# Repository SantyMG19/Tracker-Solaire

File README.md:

# Tracker-Solaire
Le Tracker Solaire est un système technologiques d'un panneau qui suit le mouvement du Soleil pour optimiser la capture d'énergie solaire.

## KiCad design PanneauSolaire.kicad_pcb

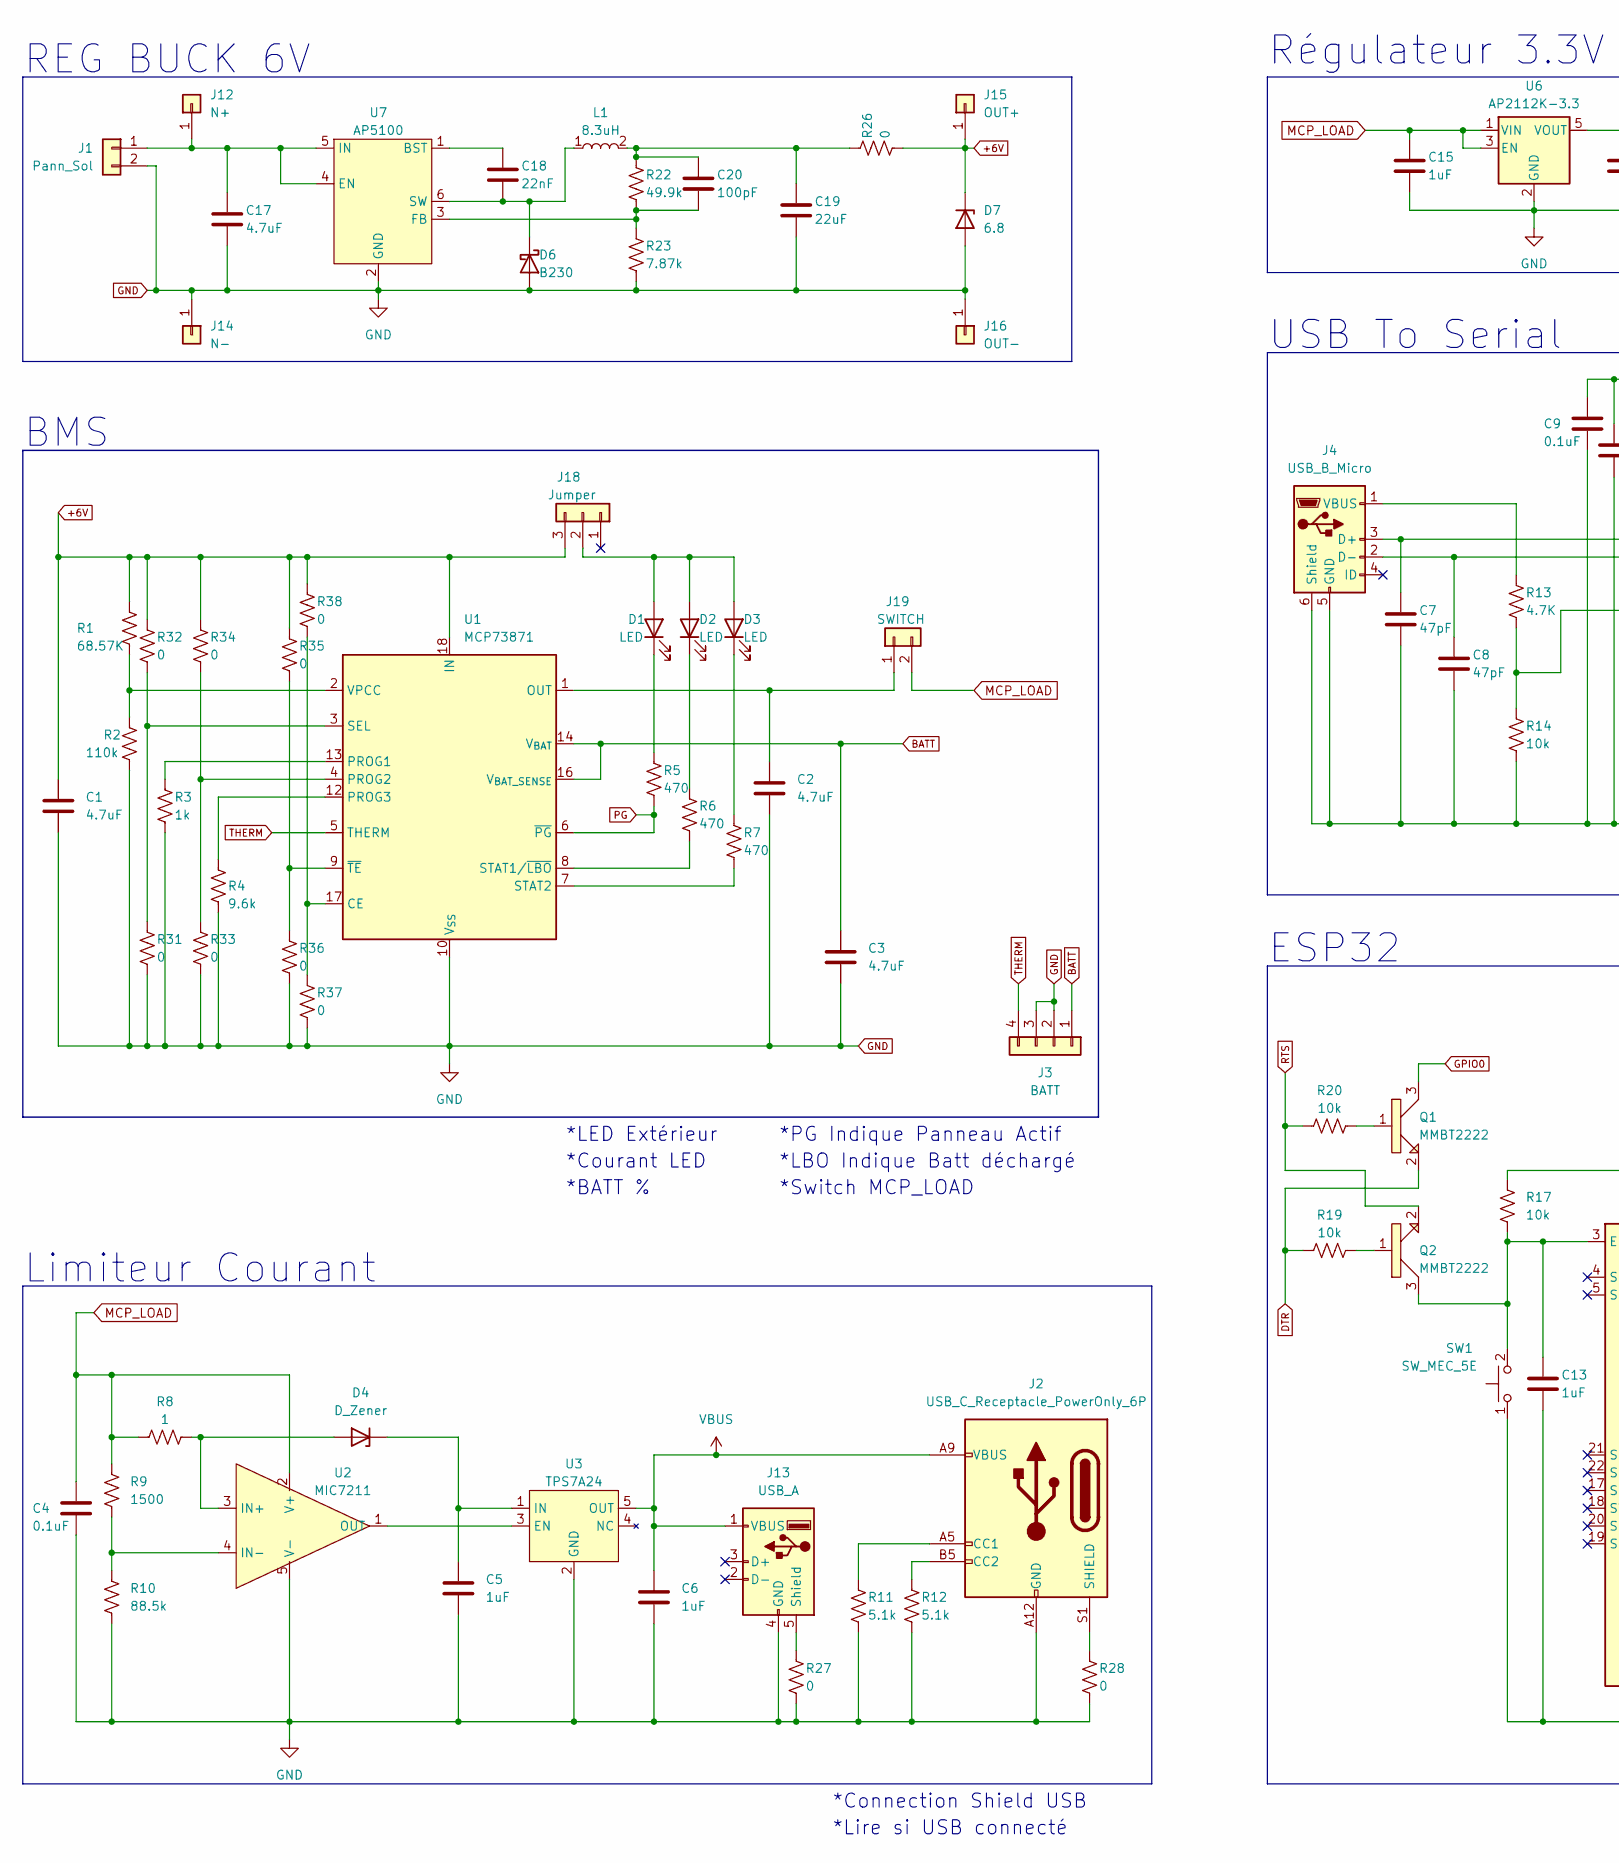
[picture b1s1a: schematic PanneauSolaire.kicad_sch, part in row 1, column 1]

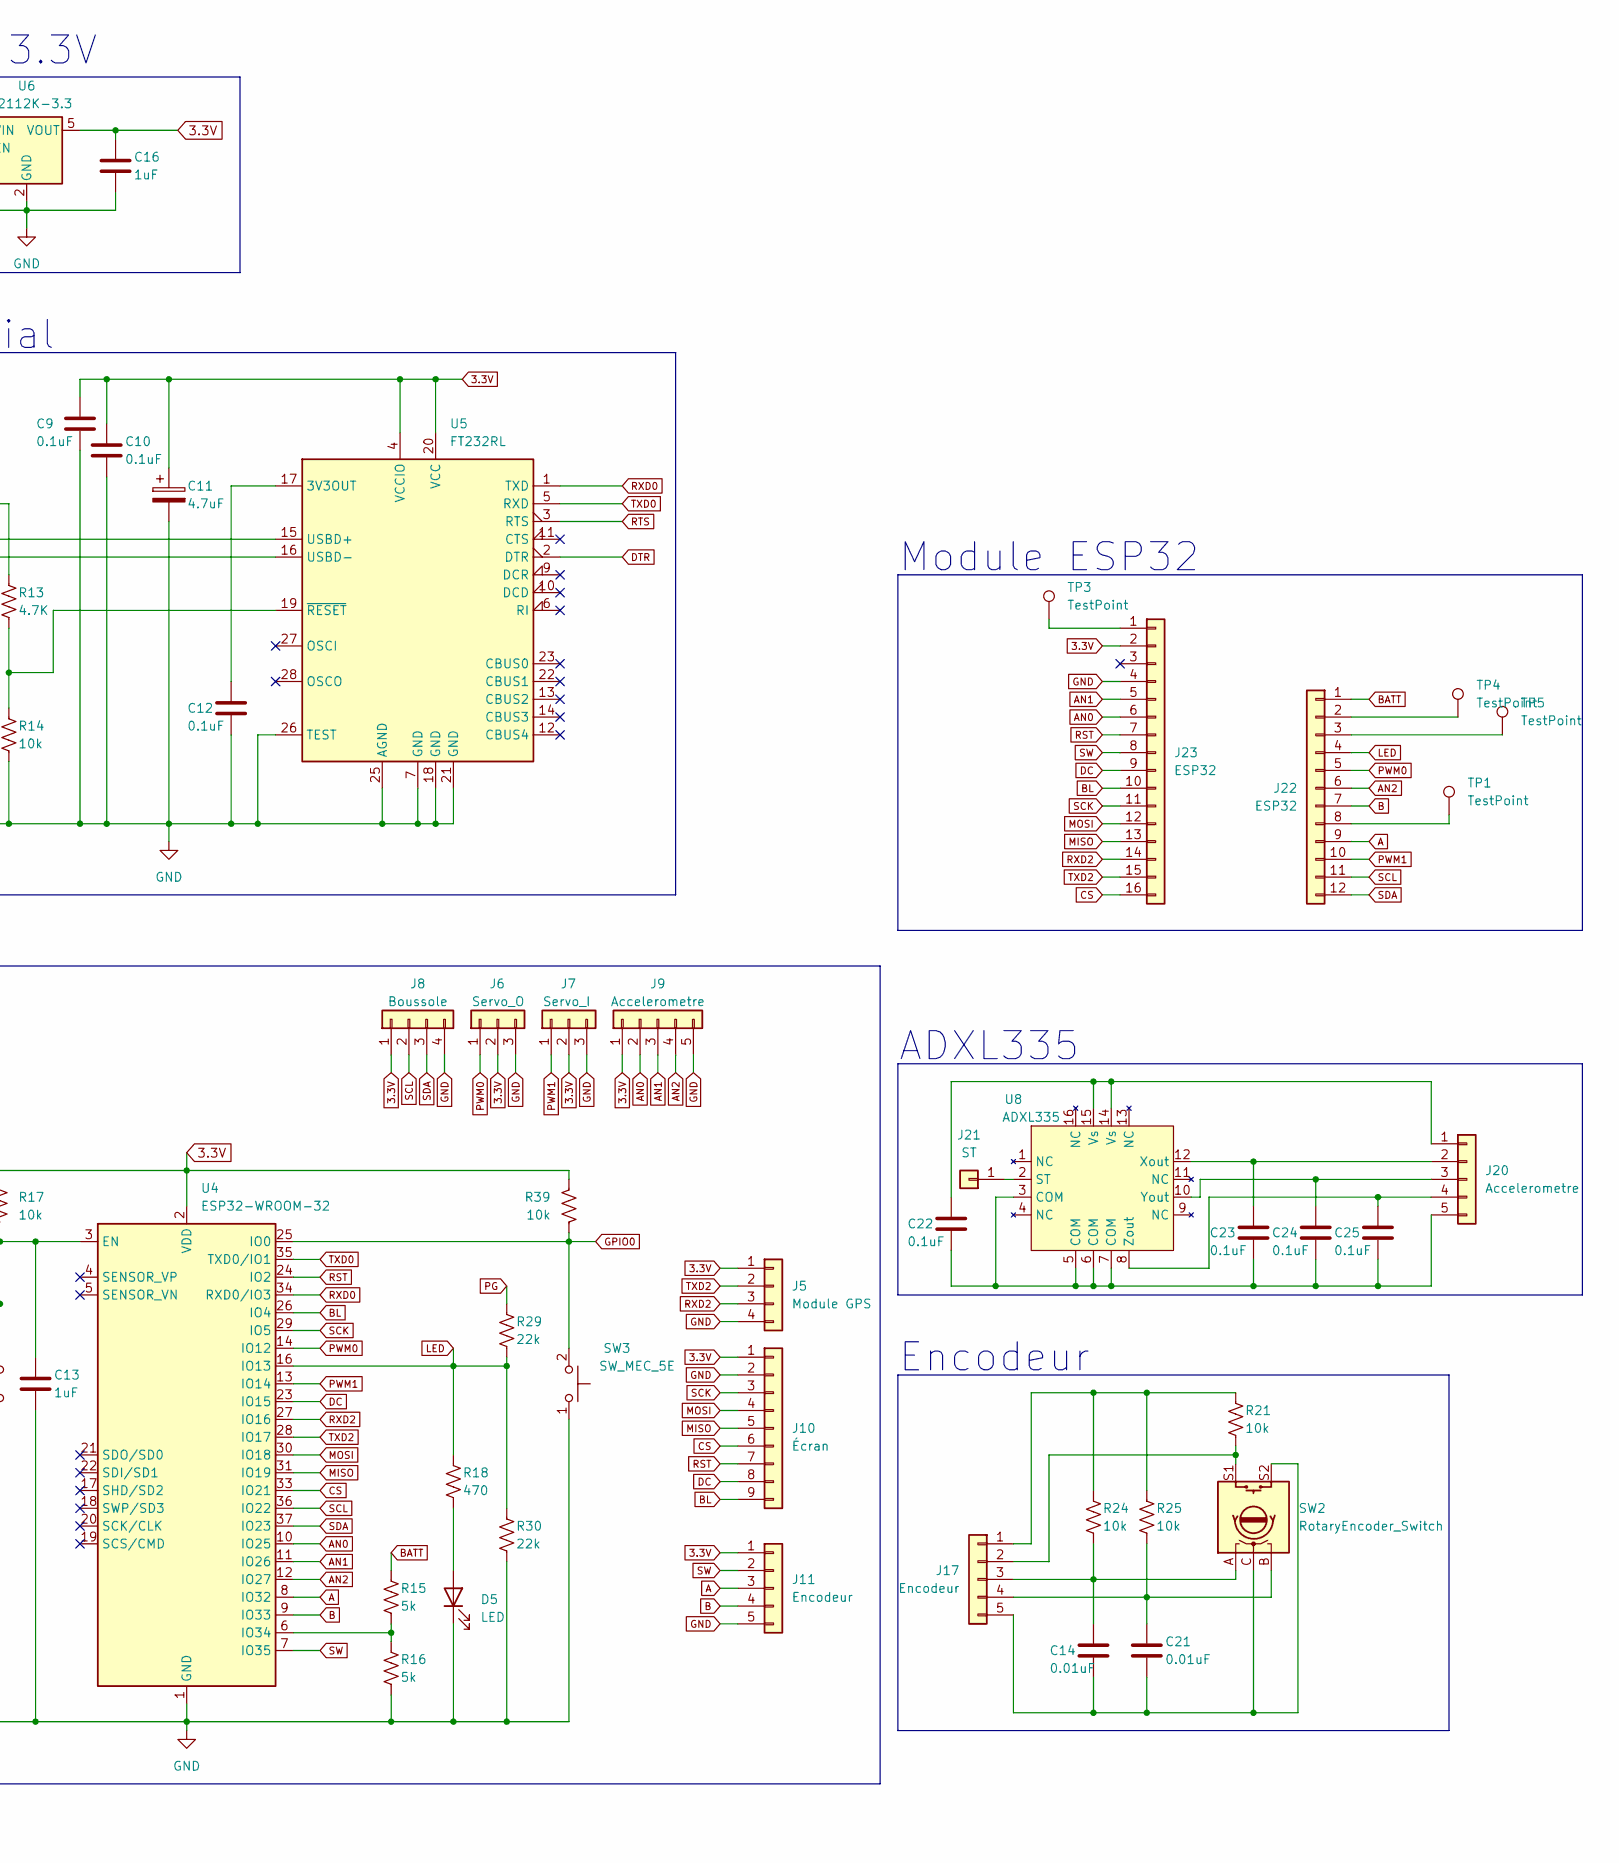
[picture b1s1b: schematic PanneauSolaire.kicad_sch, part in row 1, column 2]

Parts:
C1, C2, C3, C11, C17: 4.7uF; C_1206_3216Metric_Pad1.33x1.80mm_HandSolder
C4, C9, C10, C12, C22, C23, C24, C25: 0.1uF; C_1206_3216Metric_Pad1.33x1.80mm_HandSolder
C5, C6, C13, C15, C16: 1uF; C_1206_3216Metric_Pad1.33x1.80mm_HandSolder
C7, C8: 47pF; C_1206_3216Metric_Pad1.33x1.80mm_HandSolder
C14, C21: 0.01uF; C_1206_3216Metric_Pad1.33x1.80mm_HandSolder
C18: 22nF; C_1206_3216Metric_Pad1.33x1.80mm_HandSolder
C19: 22uF; C_1206_3216Metric_Pad1.33x1.80mm_HandSolder
C20: 100pF; C_1206_3216Metric_Pad1.33x1.80mm_HandSolder
D1, D2, D3, D5: LED; LED_0805_2012Metric_Pad1.15x1.40mm_HandSolder
D4: D_Zener; D_SOD-323_HandSoldering
D6: B230; D_SMA-SMB_Universal_Handsoldering
D7: 6.8; D_SMB_Handsoldering
J1: Pann_Sol; PhoenixContact_MC_1,5_2-G-3.81_1x02_P3.81mm_Horizontal
J2: USB_C_Receptacle_PowerOnly_6P; USB_C_Receptacle_GCT_USB4135-GF-A_6P_TopMnt_Horizontal
J3: BATT; PinHeader_1x04_P2.54mm_Vertical
J4: USB_B_Micro; USB_Micro-B_Amphenol_10118194_Horizontal
J5: Module GPS; PinHeader_1x04_P2.54mm_Vertical
J6: Servo_O; PinHeader_1x03_P2.54mm_Vertical
J7: Servo_I; PinHeader_1x03_P2.54mm_Vertical
J8: Boussole; PinHeader_1x04_P2.54mm_Vertical
J9, J20: Accelerometre; PinHeader_1x05_P2.54mm_Vertical
J10: Écran; PinHeader_1x09_P2.54mm_Vertical
J11, J17: Encodeur; PinHeader_1x05_P2.54mm_Vertical
J12: N+; PinHeader_1x01_P2.54mm_Vertical
J13: USB_A; USB_A_Molex_67643_Horizontal
J14: N-; PinHeader_1x01_P2.54mm_Vertical
J15: OUT+; PinHeader_1x01_P2.54mm_Vertical
J16: OUT-; PinHeader_1x01_P2.54mm_Vertical
J18: Jumper; PinHeader_1x03_P2.54mm_Vertical
J19: SWITCH; PinHeader_1x02_P2.54mm_Vertical
J21: ST; PinHeader_1x01_P2.54mm_Vertical
J22: ESP32; PinHeader_1x12_P2.54mm_Vertical
J23: ESP32; PinHeader_1x16_P2.54mm_Vertical
L1: 8.3uH; PA2729
Q1, Q2: MMBT2222; SC-59_Handsoldering
R1: 68.57K; R_1206_3216Metric_Pad1.30x1.75mm_HandSolder
R2: 110k; R_1206_3216Metric_Pad1.30x1.75mm_HandSolder
R3: 1k; R_1206_3216Metric_Pad1.30x1.75mm_HandSolder
R4: 9.6k; R_1206_3216Metric_Pad1.30x1.75mm_HandSolder
R5, R6, R7, R18: 470; R_1206_3216Metric_Pad1.30x1.75mm_HandSolder
R8: 1; R_1206_3216Metric_Pad1.30x1.75mm_HandSolder
R9: 1500; R_1206_3216Metric_Pad1.30x1.75mm_HandSolder
R10: 88.5k; R_1206_3216Metric_Pad1.30x1.75mm_HandSolder
R11, R12: 5.1k; R_1206_3216Metric_Pad1.30x1.75mm_HandSolder
R13: 4.7K; R_1206_3216Metric_Pad1.30x1.75mm_HandSolder
R14, R17, R19, R20, R21, R24, R25, R39: 10k; R_1206_3216Metric_Pad1.30x1.75mm_HandSolder
R15, R16: 5k; R_1206_3216Metric_Pad1.30x1.75mm_HandSolder
R22: 49.9k; R_1206_3216Metric_Pad1.30x1.75mm_HandSolder
R23: 7.87k; R_1206_3216Metric_Pad1.30x1.75mm_HandSolder
R26, R27, R28, R31, R32, R33, R34, R35, R36, R37, R38: 0; R_1206_3216Metric_Pad1.30x1.75mm_HandSolder
R29, R30: 22k; R_1206_3216Metric_Pad1.30x1.75mm_HandSolder
SW1, SW3: SW_MEC_5E; SW_SPST_PTS810
SW2: RotaryEncoder_Switch; RotaryEncoder_Alps_EC11E-Switch_Vertical_H20mm
TP1, TP3, TP4, TP5: TestPoint; PinHeader_1x01_P2.54mm_Vertical
U1: MCP73871; QFN-20-1EP_4x4mm_P0.5mm_EP2.5x2.5mm
U2: MIC7211; SOT-23-5_HandSoldering
U3: TPS7A24; SOT-23-5_HandSoldering
U4: ESP32-WROOM-32
U5: FT232RL; SSOP-28_5.3x10.2mm_P0.65mm
U6: AP2112K-3.3; SOT-23-5
U7: AP5100; SOT-23-6_Handsoldering
U8: ADXL335; LFCSP-16-1EP_4x4mm_P0.65mm_EP2.1x2.1mm

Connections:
3.3V: C9.1, C10.1, C11.1, C16.1, J5.1, J6.2, J7.2, J8.1, J9.1, J10.1, J11.1, J23.2, R17.1, R39.1, U4.2 (VDD), U5.4 (VCCIO), U5.20 (VCC), U6.5 (VOUT)
+6V: C1.1, D7.1 (K), J15.1, J18.3, R1.1, R26.2, R32.2, R34.2, R35.2, R38.2, U1.18 (IN), U1.19 (IN)
A: J11.3, J22.9, U4.8 (IO32)
AN0: J9.2, J23.6, U4.10 (IO25)
AN1: J9.3, J23.5, U4.11 (IO26)
AN2: J9.4, J22.6, U4.12 (IO27)
B: J11.4, J22.7, U4.9 (IO33)
BATT: C3.1, J3.1, J22.1, R15.1, U1.14 (V_{BAT}), U1.15 (V_{BAT}), U1.16 (V_{BAT_SENSE})
BL: J10.9, J23.10, U4.26 (IO4)
CS: J10.6, J23.16, U4.33 (IO21)
DC: J10.8, J23.9, U4.23 (IO15)
DTR: Q1.2 (EMITTER), R19.1, U5.2 (DTR)
GND: C1.2, C2.2, C3.2, C4.2, C5.2, C6.2, C7.2, C8.2, C9.2, C10.2, C11.2, C12.2, C13.2, C15.2, C16.2, C17.2, C19.2, D5.1 (K), D6.2 (A), D7.2 (A), J1.2, J2.A12 (GND), J2.B12 (GND), J3.2, J3.3, J4.5 (GND), J4.6 (Shield), J5.4, J6.3, J7.3, J8.4, J9.5, J10.2, J11.5, J13.4 (GND), J14.1, J16.1, J23.4, R2.2, R3.2, R4.2, R10.2, R11.2, R12.2, R14.2, R16.2, R23.2, R27.1, R28.1, R30.2, R31.1, R33.1, R36.1, R37.1, SW1.1, SW3.1, U1.10 (V_{SS}), U1.11 (V_{SS}), U1.21 (V_{SS}), U2.5 (V-), U3.2 (GND), U4.1 (GND), U4.15 (GND), U4.38 (GND), U4.39 (GND), U5.7 (GND), U5.18 (GND), U5.21 (GND), U5.25 (AGND), U5.26 (TEST), U6.2 (GND), U7.2 (GND)
GPIO0: Q1.3 (COLLECTOR), R39.2, SW3.2, U4.25 (IO0)
LED: J22.4, R18.1, R29.2, R30.1, U4.16 (IO13)
MCP_LOAD: C4.1, C15.1, J19.2, R8.1, R9.1, U2.2 (V+), U6.1 (VIN), U6.3 (EN)
MISO: J10.5, J23.13, U4.31 (IO19)
MOSI: J10.4, J23.12, U4.30 (IO18)
unnamed: C19.1, C20.1, L1.2, R22.1, R26.1
unnamed: D1.2 (A), D2.2 (A), D3.2 (A), J18.2
unnamed: D1.1 (K), R5.1
unnamed: D2.1 (K), R6.1
unnamed: D3.1 (K), R7.1
unnamed: D4.2 (A), R8.2, U2.3 (IN+)
unnamed: C5.1, D4.1 (K), U3.1 (IN)
unnamed: D5.2 (A), R18.2
unnamed: C18.2, D6.1 (K), L1.1, U7.6 (SW)
unnamed: C17.1, J1.1, J12.1, U7.4 (EN), U7.5 (IN)
unnamed: J2.A5 (CC1), R11.1
unnamed: J2.B5 (CC2), R12.1
unnamed: J2.S1 (SHIELD), R28.2
unnamed: C7.1, J4.3 (D+), U5.15 (USBD+)
unnamed: C8.1, J4.2 (D-), U5.16 (USBD-)
unnamed: J4.1 (VBUS), R13.1
unnamed: J13.5 (Shield), R27.2
unnamed: J17.1, R21.1, R24.1, R25.1
unnamed: J17.2, R21.2, SW2.S1
unnamed: C14.1, J17.3, R24.2, SW2.A
unnamed: C21.1, J17.4, R25.2, SW2.B
unnamed: C14.2, C21.2, J17.5, SW2.C, SW2.S2
unnamed: C2.1, J19.1, U1.1 (OUT), U1.20 (OUT)
unnamed: C22.1, J20.1, U8.14 (Vs), U8.15 (Vs)
unnamed: C23.1, J20.2, U8.12 (Xout)
unnamed: C24.1, J20.3, U8.10 (Yout)
unnamed: C25.1, J20.4, U8.8 (Zout)
unnamed: C22.2, C23.2, C24.2, C25.2, J20.5, U8.3 (COM), U8.5 (COM), U8.6 (COM), U8.7 (COM)
unnamed: J21.1, U8.2 (ST)
unnamed: J22.2, TP4.1
unnamed: J22.3, TP5.1
unnamed: J22.8, TP1.1
unnamed: J23.1, TP3.1
unnamed: Q1.1 (BASE), R20.2
unnamed: Q2.1 (BASE), R19.2
unnamed: C13.1, Q2.3 (COLLECTOR), R17.2, SW1.2, U4.3 (EN)
unnamed: R37.2, R38.1, U1.17 (CE)
unnamed: R3.1, U1.13 (PROG1)
unnamed: R33.2, R34.1, U1.4 (PROG2)
unnamed: R4.1, U1.12 (PROG3)
unnamed: R31.2, R32.1, U1.3 (SEL)
unnamed: R6.2, U1.8 (STAT1/~LBO)
unnamed: R7.2, U1.7 (STAT2)
unnamed: R1.2, R2.1, U1.2 (VPCC)
unnamed: R35.1, R36.2, U1.9 (~TE)
unnamed: R9.2, R10.1, U2.4 (IN-)
unnamed: U2.1 (OUT), U3.3 (EN)
unnamed: R15.2, R16.1, U4.6 (IO34)
unnamed: C12.1, U5.17 (3V3OUT)
unnamed: R13.2, R14.1, U5.19 (~RESET)
unnamed: C18.1, U7.1 (BST)
unnamed: C20.2, R22.2, R23.1, U7.3 (FB)
PG: R5.2, R29.1, U1.6 (~PG)
PWM0: J6.1, J22.5, U4.14 (IO12)
PWM1: J7.1, J22.10, U4.13 (IO14)
RST: J10.7, J23.7, U4.24 (IO2)
RTS: Q2.2 (EMITTER), R20.1, U5.3 (RTS)
RXD0: U4.34 (RXD0/IO3), U5.1 (TXD)
RXD2: J5.3, J23.14, U4.27 (IO16)
SCK: J10.3, J23.11, U4.29 (IO5)
SCL: J8.2, J22.11, U4.36 (IO22)
SDA: J8.3, J22.12, U4.37 (IO23)
SW: J11.2, J23.8, U4.7 (IO35)
THERM: J3.4, U1.5 (THERM)
TXD0: U4.35 (TXD0/IO1), U5.5 (RXD)
TXD2: J5.2, J23.15, U4.28 (IO17)
VBUS: C6.1, J2.A9 (VBUS), J2.B9 (VBUS), J13.1 (VBUS), U3.5 (OUT)

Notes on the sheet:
*Lire si USB connecté
*BATT %
*Connection Shield USB
Module ESP32
*PG Indique Panneau Actif
ESP32
*Switch MCP_LOAD
*LBO Indique Batt déchargé
Limiteur Courant
BMS
Régulateur 3.3V
*Courant LED
USB To Serial
REG BUCK 6V
*LED Extérieur
Encodeur
ADXL335

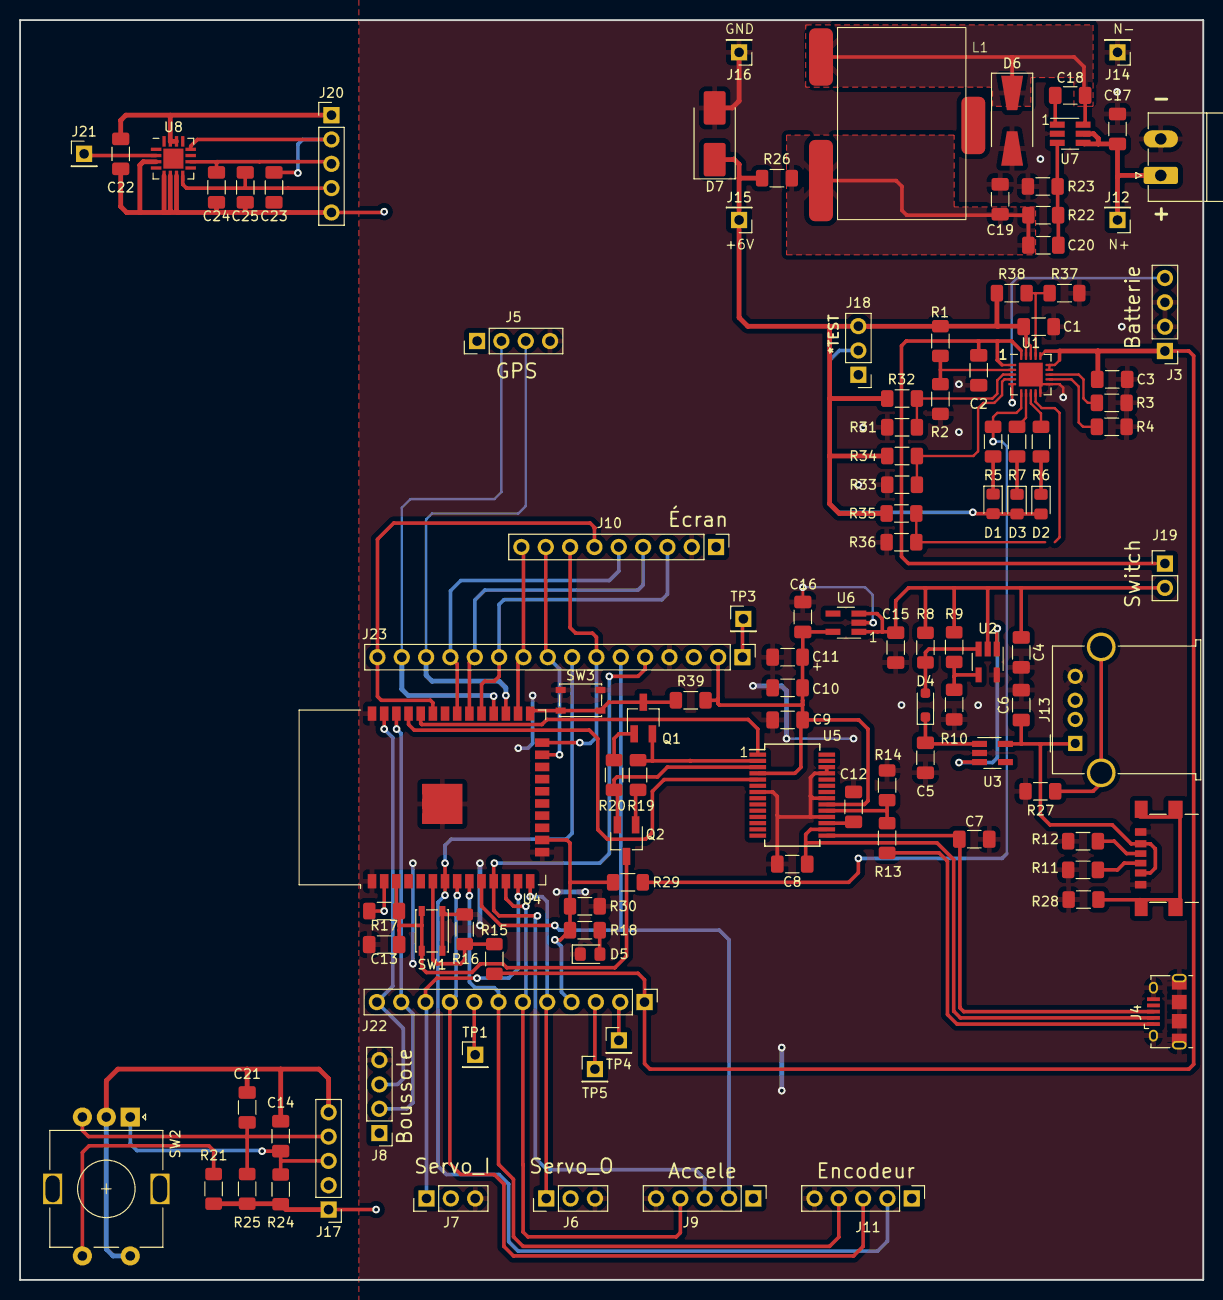
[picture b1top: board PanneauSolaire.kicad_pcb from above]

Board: 2 copper layers, 123.5 x 131.5 mm, 112 parts (0 on the bottom side), 85 nets.

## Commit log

2024-05-23 Create Impressions_3D
2024-05-23 téléchargement fichiers Impression 3D
2024-05-23 Schéma projet
2024-05-23 PCB projet
